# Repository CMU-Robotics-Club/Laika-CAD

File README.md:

# Laika-CAD
 Quadruped Project CAD Repo

## 1: Description
This repo contains all the CAD for the CMU Robotics Club Quadrupeds Project. All CAD files, whether for the robot itself, a prototype, test structures, unused designs, or anything else should live within this repo. The CAD software of choice is SOLIDWORKS; non-SOLIDWORKS files should ideally be converted when possible or clearly marked with their respective software if conversion is problematic. The overall structure follows National Robotics Engineering Center EPDM standards as detailed below.

## 2: File Locations
The top level of CAD should only contain file folders and the top-level full assembly. Folders are created for submodules (legs, drivetrain, chassis, etc.) and for component types. COTS (Commercial Off-The-Shelf) components should be identified in a COTS folder; if generic enough to have application in multiple submodules, they should live in top-level COTS. The top-level COTS includes subdirectories for component types (fasteners, bearings, etc.). If a subdirectory appropriate for a part does not exist, create one. Note that these subdirectories should have more within them (for example, a FASTENERS subdir should contain BOLTS, NUTS and NUTS should contain NYLOC, PEM, JAM) If the COTS component is highly specific, should exist in lower level COTS folder in submodule directory. Files should generally be separated by file classifiers (see below). Top-level submodule directories should only contain 900-level files and 200-level files that belong to no subassembly. 200-level files which are part of subassemblies should be organized into descriptive subdirectories. All other file levels should be organized into subdirectories within the submodule directory (e.g. a simulation for a drive train motor shaft should be within a SIMULATION folder placed in the same directory as the top-level assembly for the drive train submodule). 000, 100, 400 series files should live within MANUFACTURING, DRAWINGS, and SIMULATION folders respectively placed within the same directory as the subassembly to which the relevant parts belong to.

## 3: File Naming
### 3.1: Custom
Custom parts should obey the XXXX YZZ - NAME file number convention:  
XXX: Module ID (Alphabetical)   
Y: File type classifier (Numbers)   
ZZ: Part number (Numbers)   
NAME: Descriptive file name in Title Capitalization Form     

Example:
CYC 208 - Gearbox Mount Plate

The Module ID is an up-to-four-character code that describes the module the file belongs to. Should be as descriptive as four characters allow. The list of current module classifiers can be seen below:  
LAIK: Top-level assembly  
CHAS: Chassis  
DRIV: Drive train  
CYC: Cycloidal gearbox  
LEG: Leg design  
MTST: Motor test rig  
LTST: Leg test rig  

Please maintain this list as the project scope evolves.

The file type classifiers are as follows:  
0: Manufacturing file formats (STL, DXF, GCODE, etc.)  
1: Drawings  
2: Individual parts  
3: Equation .txt files  
4: Solidworks FEA Simulation Files  
5: Jigs/tools related to the assembly/manufacture of another part  
6: Weldments  
7: Piping, tubing, wiring, related  
8: Subassemblies  
9: Top-level assemblies. Typically no more than one (plus configurations) per module  

Please update this list as the scale of the project evolves.  

Part numbers should be defined beginning at 01. Number parts as they are created regardless of complexity, dependency, etc. Ensure that each part number for a given file type is only used once per subassembly. If you have more than 99 parts in a subassembly, you are doing something wrong!

Example:  
The completed drive train assembly would be named DRIV-901 - Drive Train Assem and would exist in the top-level DRIVE TRAIN folder.  
The housing subassembly would be DRIV-801 - Drive Train Housing and would exist in the lower-level DRIVE TRAIN/HOUSING folder.  
The drawing for one of the housing components would be DRIV-105 - Drive Train Top Cover and would exist in the DRIVE TRAIN/DRAWINGS folder.

### 3.2: COTS
COTS (Commercial Off-The-Shelf) parts should be named descriptively but do not need original part numbers. McMaster parts can be left as named when exporting as SLDPRT. Non-McMaster parts should be named descriptively, typically including part type, key dimensions, material as appropriate, etc. Additionally, should include manufacturer and part number. Use your best judgement! Someone with no project experience should be able to, from the file name, tell what the part is and where to order it.

### 3.3: Directories

Directories should be named in ALL CAPS. They should be named to describe the subassembly, component type, etc.

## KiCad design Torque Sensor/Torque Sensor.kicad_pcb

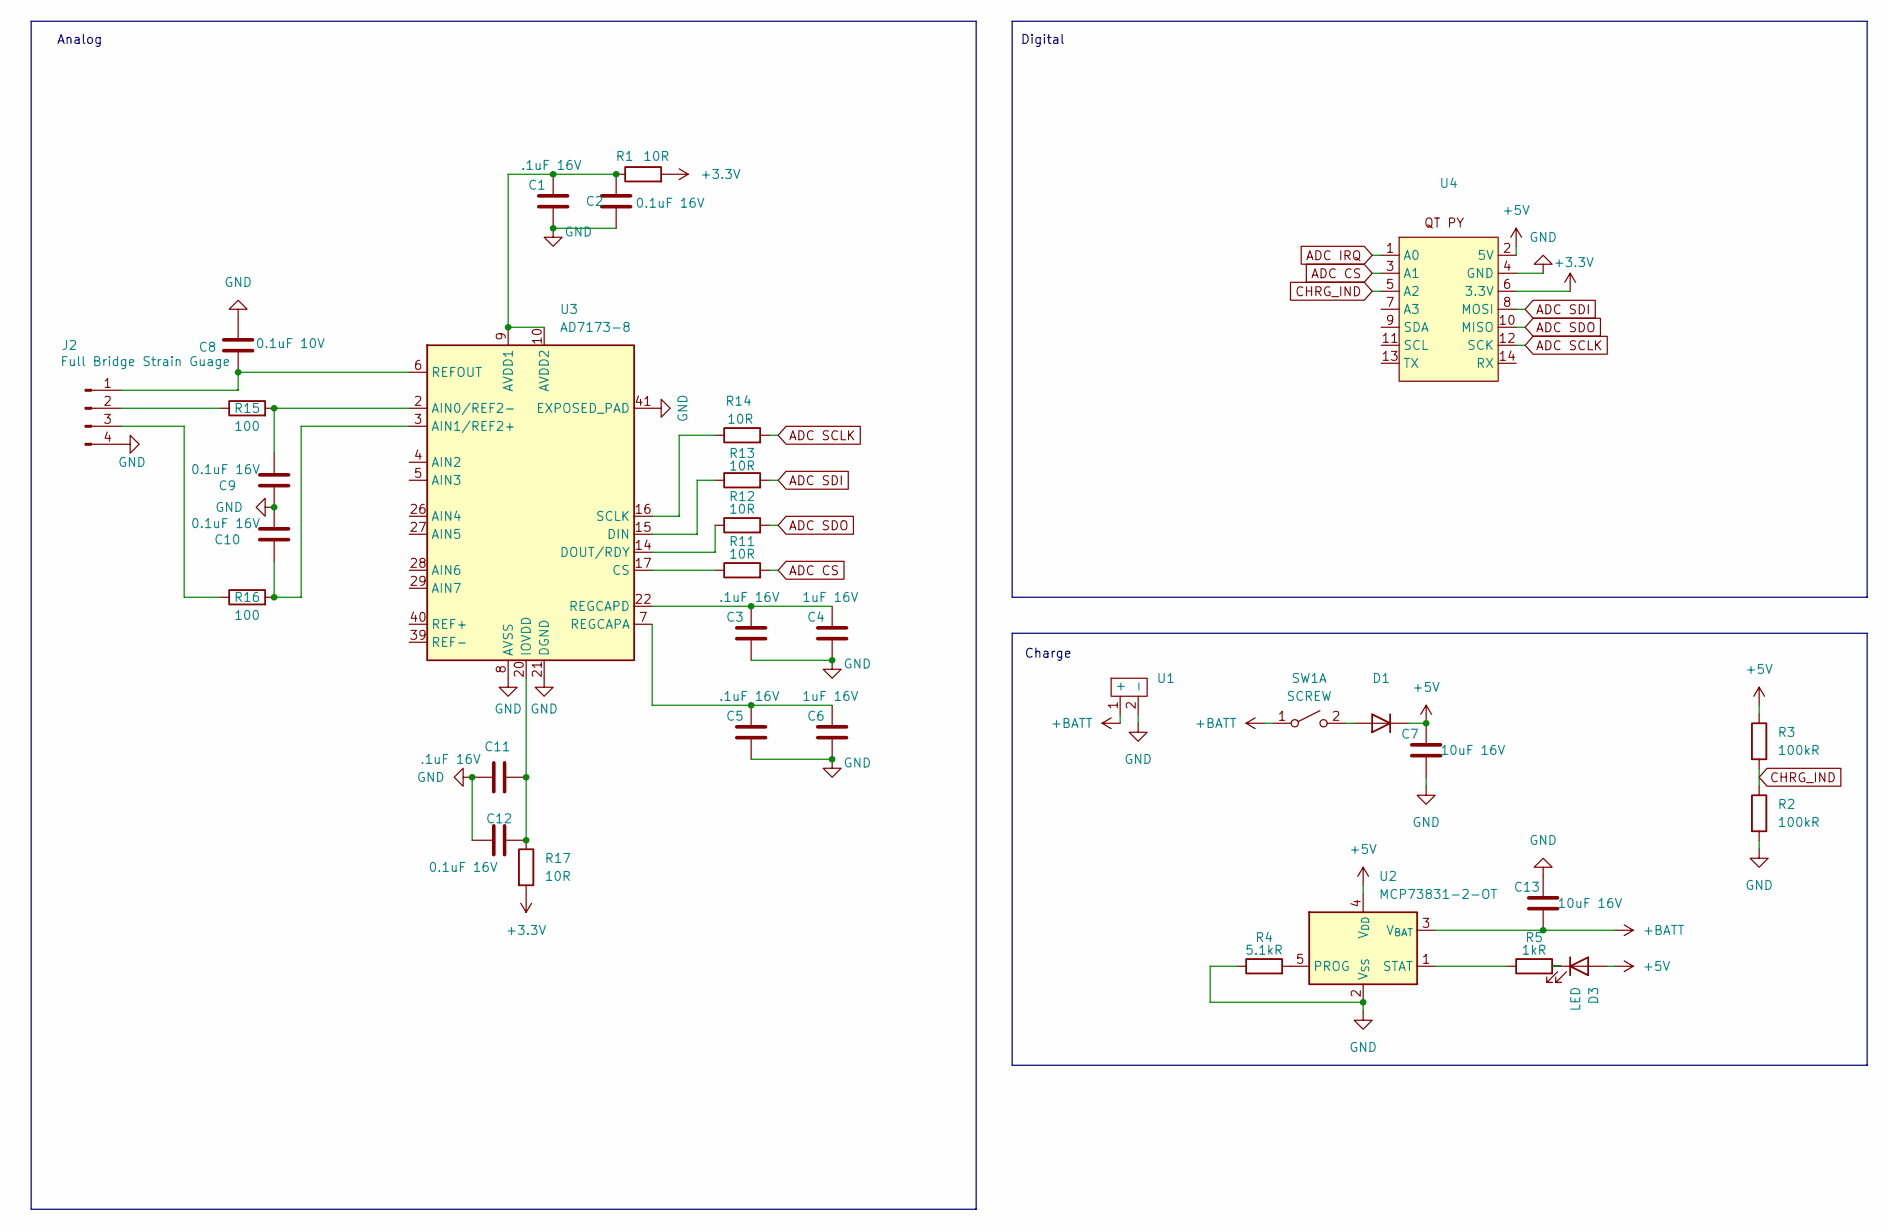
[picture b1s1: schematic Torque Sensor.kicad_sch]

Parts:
C1, C3, C5, C11: .1uF 16V; C_0805_2012Metric
C2, C9, C10, C12: 0.1uF 16V; C_0805_2012Metric
C4, C6: 1uF 16V; C_0805_2012Metric
C7, C13: 10uF 16V; C_0805_2012Metric
C8: 0.1uF 10V; C_0805_2012Metric
D1: D_SOD-323
D3: LED; LED_0805_2012Metric
J2: Full Bridge Strain Guage; PinHeader_1x04_P1.00mm_Vertical
R1, R11, R12, R13, R14, R17: 10R; R_0805_2012Metric
R2, R3: 100kR; R_0805_2012Metric
R4: 5.1kR; R_0805_2012Metric
R5: 1kR; R_0805_2012Metric
R15, R16: 100; R_0805_2012Metric
SW1: SCREW; PinHeader_1x02_P1.00mm_Vertical
U1: test
U2: MCP73831-2-OT; SOT-23-5
U3: AD7173-8; LFCSP-40-1EP_6x6mm_P0.5mm_EP3.9x3.9mm
U4: Adafruit QT PY

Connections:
+3.3V: R1.2, R17.2, U4.6 (3.3V)
+5V: C7.2, D1.1 (K), D3.2 (A), R3.1, U2.4 (V_{DD}), U4.2 (5V)
+BATT: C13.1, SW1.1 (A), U1.1 (+), U2.3 (V_{BAT})
ADC CS: R11.2, U4.3 (A1)
ADC IRQ: U4.1 (A0)
ADC SCLK: R14.2, U4.12 (SCK)
ADC SDI: R13.2, U4.8 (MOSI)
ADC SDO: R12.2, U4.10 (MISO)
AVDD: C1.2, C2.2, R1.1, U3.4 (AVDD), U3.9 (AVDD1), U3.10 (AVDD2), U3.40 (AVDD)
CHRG_IND: R2.1, R3.2, U4.5 (A2)
unnamed: D1.2 (A), SW1.2 (B)
unnamed: D3.1 (K), R5.2
unnamed: C8.1, J2.1, U3.6 (REFOUT)
unnamed: J2.2, R15.1
unnamed: J2.3, R16.1
unnamed: R4.2, U2.5 (PROG)
unnamed: R5.1, U2.1 (STAT)
unnamed: C9.2, R15.2, U3.2 (AIN0/REF2-)
unnamed: C10.1, R16.2, U3.3 (AIN1/REF2+)
unnamed: R11.1, U3.17 (CS)
unnamed: R13.1, U3.15 (DIN)
unnamed: R12.1, U3.14 (DOUT/RDY)
unnamed: C11.2, C12.2, R17.1, U3.20 (IOVDD)
unnamed: C5.2, C6.2, U3.7 (REGCAPA)
unnamed: R14.1, U3.16 (SCLK)

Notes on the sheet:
Analog
Charge
Digital

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
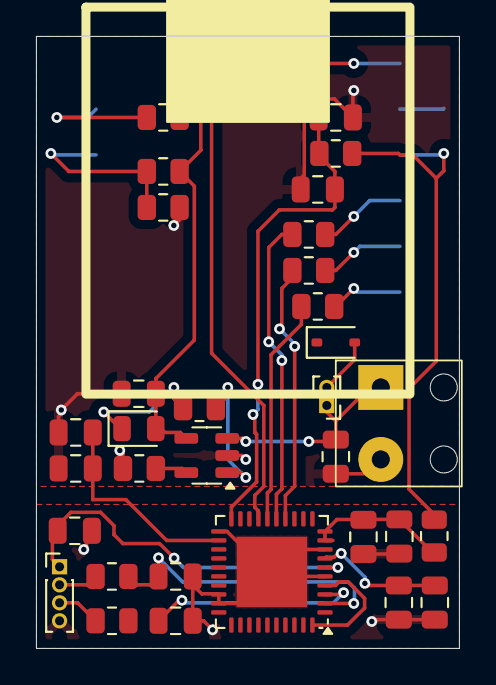
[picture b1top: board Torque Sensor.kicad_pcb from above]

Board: 2 copper layers, 23.5 x 34.0 mm, 33 parts (0 on the bottom side), 26 nets.

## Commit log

2023-12-11 Initialized, added files
    Added files with NREC EPDM organization, updated readme.
2023-12-11 Updated file names
2023-12-11 Finished file names
2023-12-12 Updated drive train design, added housing assem
2023-12-13 Finalized drive
2023-12-13 nothin
2023-12-28 create folder for cycloidal
2023-12-28 Cycloidal Disk
2023-12-28 Eccentric nut
2023-12-28 added weird standoff thing
2023-12-31 Updated files and readme
2023-12-31 Fixed readme
2024-01-05 added thrust bearing to readme
2024-01-05 added pin circle diam to readme
2024-01-19 beginning 14 drive
2024-01-26 folder for solidworks made
    this is gonna be a mess for now, ill format it later
2024-01-28 fixing blatant misinformation
2024-01-28 idk i just got dumped but heres some cad :)
2024-01-28 i did some more stuff
    the rolly torque transmition things are missing, any screws, and the thrust bearing. also all the clearances must be found
2024-01-28 got rid of the nasty stuff
2024-01-28 did some sheisse idk i forgor
2024-01-28 added load pins
2024-01-28 got rid of cringe
2024-01-28 misinformation warning
2024-01-30 adjusted clearances
    clearances to find left:
    - change gear clearance thing
    - ball bearing clearance (the actual balls)
2024-01-30 added colors
    see previous commit for what to do next
2024-01-31 did the stuf i said i woudl do
2024-02-03 minor stuff
2024-02-10 among us haha
2024-02-11 fixed some dimension stuff
    a lot is like still fucked
2024-02-17 i did stuff lmao
2024-02-17 pee pee poo poo
2024-02-17 goobye
2024-02-24 leg design beginning
2024-03-15 clearance stuff
2024-03-21 added laser files
2024-04-06 leg stuff
2024-04-06 random stuff
2024-04-06 fixed leg
2024-04-06 leg 2 double pulley edition
2024-04-18 i am sane and can be trusted around automobiles
2024-04-20 Add lower plate file via upload
2024-04-20 Rename LEG 203 - Lower Plate.SLDPRT to LEG 204 - Lower Plate.SLDPRT
2024-04-20 Lower leg plate files
2024-04-20 Lower leg assembly file
2024-04-20 leg leg leg
2024-07-05 renamed stuff
    assembly is still broken
2024-07-11 fixed equation dependency
2024-07-18 renamed parts, also motor mount stuff
2024-09-08 i am dumb
    asdfadgsadasfggawagregareagr
2024-09-13 sometig happened
2024-09-17 Rough Hinge Draft
2024-09-17 draft
2024-09-17 stas
2024-09-17 Add fan files
2024-09-17 add STL
2024-09-17 Knee motor mounting position change
2024-09-23 Sheet metal
2024-09-23 Modify snap loationc
2024-09-23 lightening
2024-09-30 add fan model
2024-09-30 add odrive motor driver model
2024-10-01 updated shaft clearance
2024-10-04 add odrive model, change names to CYC
2024-10-05 Forearm
2024-10-05 Side Fan Cover
2024-10-08 Add Chassis
2024-10-08 combine side cover
2024-10-09 git commit whatever the fuck i did these few days idk i forgor
2024-10-09 added gitignore
    im such a sussy baka
2024-10-09 removed squiggly and added gitignore to this branch to kill more squiggly
2024-10-09 File Names Fixed
2024-10-10 90degree bend added to leg joint
2024-10-10 lighter
2024-10-10 equations and middle plate thingy
2024-10-11 merged with William's
2024-10-11 Initial Chassis Setup
2024-10-12 Leg Spacing Fixed
2024-10-22 smtn
2024-10-22 Created CHA-202-Battery Carriage
    wip funny stuff
2024-10-22 the purge
2024-10-22 saved one (1) (I) file
2024-10-22 merged hip williaM INTO BODy danya
2024-10-23 started working more on body
    todo
    - make the position of the "holes" for motor mount on the front plate be derived from that of the middle plates
2024-10-24 leg modifications
2024-10-25 Added CF shoulder plate to main assembly
2024-10-25 Actually added the plates
2024-10-29 Updated carriage temp file
2024-10-29 Added New Spacer on top
2024-10-30 Elbow Joint Motor Mounting Finished
2024-10-30 Upper Pulley tweaks
2024-10-30 Made file bases
    awooga made new files to model 3d parts off of
2024-11-05 Base sketch of rib dimensions
    I learned about linked and global dimensions and am on the way to a nice customizeable and controllable rib part
2024-11-05 upper hip polished up
2024-11-05 Middle Plate Reparameterized, Battery Rib WIP
    Redid the middle plate so that all its functional dimensions (excluding for now the motor cutouts) are completely described by global variables in 301. Battery plate WIP, currently using these variab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
2024-11-05 Conclusion to middle plate, rib continues
    continueing the rib. battery sadly at 6%
2024-11-05 Deleted Body Mockup for Body integration
2024-11-05 back plate assembly
2024-11-05 Screw ports modeled
    adddd 3%
2024-11-05 deleted meche HW
2024-11-06 Merged with William Leg 11/5
2024-11-06 half done Sprocket revision - assemblies broken
2024-11-06 Assembly Errors fixed
2024-11-06 The RIB gets a WIP upper clip
    it's starting to figure out how to attach to several bars, the two carbon fiber ones on top as well as supporting on the bottom
2024-11-06 changing plate shapes
2024-11-08 Spacers added and more tightening up (not done)
2024-11-09 Tensioning System Progress+ Upper Spacers Modeled
2024-11-09 Added Tensioner
2024-11-09 set positions of gearboxes
2024-11-12 Massed Parts
2024-11-12 file name changes and also variable stuff
2024-11-12 First Batch of Merges and Nomenclature
    Merged Danya's work into pieces, reworked all files to have right nomenclature.
2024-11-12 more variable stuff
2024-11-12 driven dimension shtufff
2024-11-12 added side snap panel
    the side mount plate should be multiple parts, the largest being lasercut acrylic, and the clips would be glued on petg
2024-11-13 RAH! Continued development!
    Figuring shit out!!!
2024-11-13 update body
2024-11-15 comkit
2024-11-15 Changes to the Old Assembly
    - removed rods
    - separate CF tube for bottom front and back
2024-11-16 Added CF plates
2024-11-18 Cross shape plate mock up
2024-11-18 No idea but funny colors
2024-11-19 flat bottom
2024-11-19 wagh! committing recent changes
2024-11-22 battery belly
2024-11-23 added divider plates
2024-11-23 nothing :)
2024-11-23 init
2024-11-23 Added roof plate, battery door, and fixes CHAS to CHA
2024-11-24 progress check -- all assemblies broken
2024-11-24 Inital version finished
2024-11-24 bad stuff deleted
2024-11-24 Thiccer legs
2024-11-24 Literially no idea what is going on (GOD?)
2024-11-25 god again :(
2024-11-27 update fansnaps, new side fan cover
2024-12-03 Revert "driven dimension shtufff"
    This reverts commit ce57025ba4d824377ffcb4c915e27c631bb65429.
2024-12-03 renamed files
2024-12-03 what
2024-12-03 moved stl
2024-12-03 idk what broke all this oy vey
2024-12-03 removed bottom tube, made front and back plates shorter
2024-12-07 Carbon fiber top and bottom plates
2024-12-11 Upper Arm assembly streamlined
2024-12-13 Plates redone
2024-12-13 changed holes for cf tubes and added plug
2024-12-13 added support plates, and battery top plate
2024-12-13 added gearmotor configurations
2024-12-13 made temporary assembly to see how legs look w chassis
2024-12-13 Knee Padding/Guards
2024-12-14 Changed Chainguard geometry
2024-12-14 Knee motor cover
2024-12-14 transient files deleted
2024-12-14 Added Spacers for azimuth sprockets
2024-12-16 Added mounting for knee pads
2024-12-16 Knee Motor Cover bolt holes added
2024-12-17 lightening stuff, and nut strip stuff
2024-12-19 Mount holes for guards and box mount for mature
2024-12-19 mount bracket holes spacing fixed
2024-12-20 tolerences added
2024-12-26 Forarm Endstop added, interference fixed
2024-12-29 gearbox updates
    need to fix spacing between gears and thrust bearing, also increase length of output
2024-12-30 Added Electronics Mockup
2024-12-30 Minor transformations
2024-12-30 update on router
2024-12-30 Tube plug fixed, bottom odrive flipped, top sprocket spacer modified
2024-12-31 todo list half done
    TPU foot, Bottom Odrive Flipped, motor mounting redone
2024-12-31 todo list done
    fan vent holes added.
2025-01-09 work in progress
2025-01-09 Fixed Limit switch constraints
2025-01-12 Changed Sheet Metal Motor mount geometry
2025-01-15 lightened gearbox, added holes for captive nuts
2025-01-18 some stuff
2025-01-18 Fixed Merge with leg-static-knee-motor
2025-01-18 cleaned up gearbox
2025-01-19 added flange to ball bearing jig
2025-01-24 made some changes
2025-01-24 adjusted ball bearing drilling jig
2025-01-24 ball bearing jig
2025-01-24 adjusted eccentric gear
2025-01-25 dxf changes
2025-01-25 adjusted gear scale
2025-01-25 gear box clearance
2025-01-25 gewear box clearancre
2025-01-25 made bearing less tight
2025-01-29 updated top lid dxf
2025-01-29 new part of top hat bruh
2025-01-30 designed jig for
2025-01-30 fixed name
2025-02-08 eccentric gear clearance
2025-02-08 battery box update
2025-02-08 tighter gwar
2025-02-13 removed entire gear clearance
2025-02-13 Clearance and tolerance fixes to spacers
2025-02-15 flanged d shaft
2025-02-16 more progress on the battery box
2025-02-19 eccentric shaft stl
    apparently wasnt supposed to have 2025 access lmao
2025-02-19 stuff
    i made this bc solidworks is greedy and makes their software unuseable because money
2025-02-19 fixing stuff
2025-02-19 reversing some 2025 damage
2025-02-20 added screws and nuts
2025-02-20 added parts
2025-02-20 more parts
2025-02-20 gearmotor stuff
2025-02-20 some more changes
2025-02-21 more work on the battery box
2025-02-21 body work
2025-02-24 more work on body
2025-02-24 hinge upgrade
2025-02-27 gearbox cover (just cosmetic)
    covers up ugliness ig
2025-03-01 Fixed faulty Sprocket Guard Geometry
2025-03-07 fixes
2025-03-10 redid the flanged shaft post-2025 solidworks incident
2025-03-11 broke a lot of things, will fix soon
2025-03-13 flanged shaft stuff
2025-03-14 parts for testing
2025-03-15 Updated Knee Motor Cover for new gearbox mounts and limit switch
2025-03-15 drawings of the eccentric nut
2025-03-15 part 209 drawing
2025-03-15 removed bolt holes in shaft as it is not necessary
2025-03-15 adjusted slot size to 5/16ths
2025-03-17 kill
2025-04-09 I created a functioning assembly
    madethe tubes line up
2025-06-20 more mature parts
2025-06-20 Revert "more mature parts"
    This reverts commit 7416bf9d5b08666f80eef6642ade20d691233d97.
2025-06-23 added dowel pin holes to main body
2025-06-24 added more pin holes
2025-06-24 slip fit for top lid
2025-08-20 added soft jaws cad for manufacturing eccentric shaft
2025-09-12 Torque Sensor KiCAD
2025-09-12 Reverted to older schematic
2025-09-12 updated nets
2025-09-17 Changed board to Feather rp2040 for charging circuitry, assigned footprints to caps and resistors.
2025-09-17 Changed ADC to the more JLC stocked AD7173-8 (Rev. B)
2025-09-18 Rolled back to using QTPY with new charging circuitry
2025-09-23 Better style - connections explicitly shown.
2025-10-03 Designed PCB for torque sensor
2025-10-15 Cyclodial Gearbox V2
2025-10-29 Alignment holes and tolerancing
2025-10-29 created new branch for cycloidal v2
2025-10-30 flipped QTPY to back
2025-10-31 Spacers
2025-10-31 seperate parts for shaft
2025-11-16 2024 solidworks version
2025-11-20 wow new gearbox tweaks so awesome
2025-11-23 changed number of holes 5->4
